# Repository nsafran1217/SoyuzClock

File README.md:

# SoyuzClock
Recreation of the 744H clock that flew on Soyuz space capsules

This is meant to be an accurate replica of the Soyuz 744H clock as feature on CuriousMarc's youtube channel.

- `SoyuzControlBoard` contains the KiCAD files for the esp32 board. There are many components that are optional.

- `SoyuzLedBoard` contains the KiCAD files for the board that the LED display mount on.

- `Soyuz-esp32` contains the PlatformIO project that runs the clock

## Part numbers
- АЛС324А is the 7 segment LED display. They are available on eBay or at tubes-store.com. They have the same quality issues as found in the real clock.

- МТ-1 is the toggle switch. They are available on eBay.

- ПКн2-1 is the correct push button, however, they are hard to find in the west. I found some stores selling them in Ukraine and Russia, but each switch is at least $15 US, plus you need to convince the seller its worth their time to ship it to you.

- KM1-1 is the next best option. They are easily found on eBay. The push button is smaller than the real switch. This is what I am using for now.

# 
Thanks to Curious Marc for documenting this clock: https://www.curiousmarc.com/space/soyuz-clock-744h-digital

I made a recreation of the case in FreeCAD based HEAVILY on this FreeCAD design: https://grabcad.com/library/soyuz-spacecraft-clock-1

This design will be added to this repo when finalized.

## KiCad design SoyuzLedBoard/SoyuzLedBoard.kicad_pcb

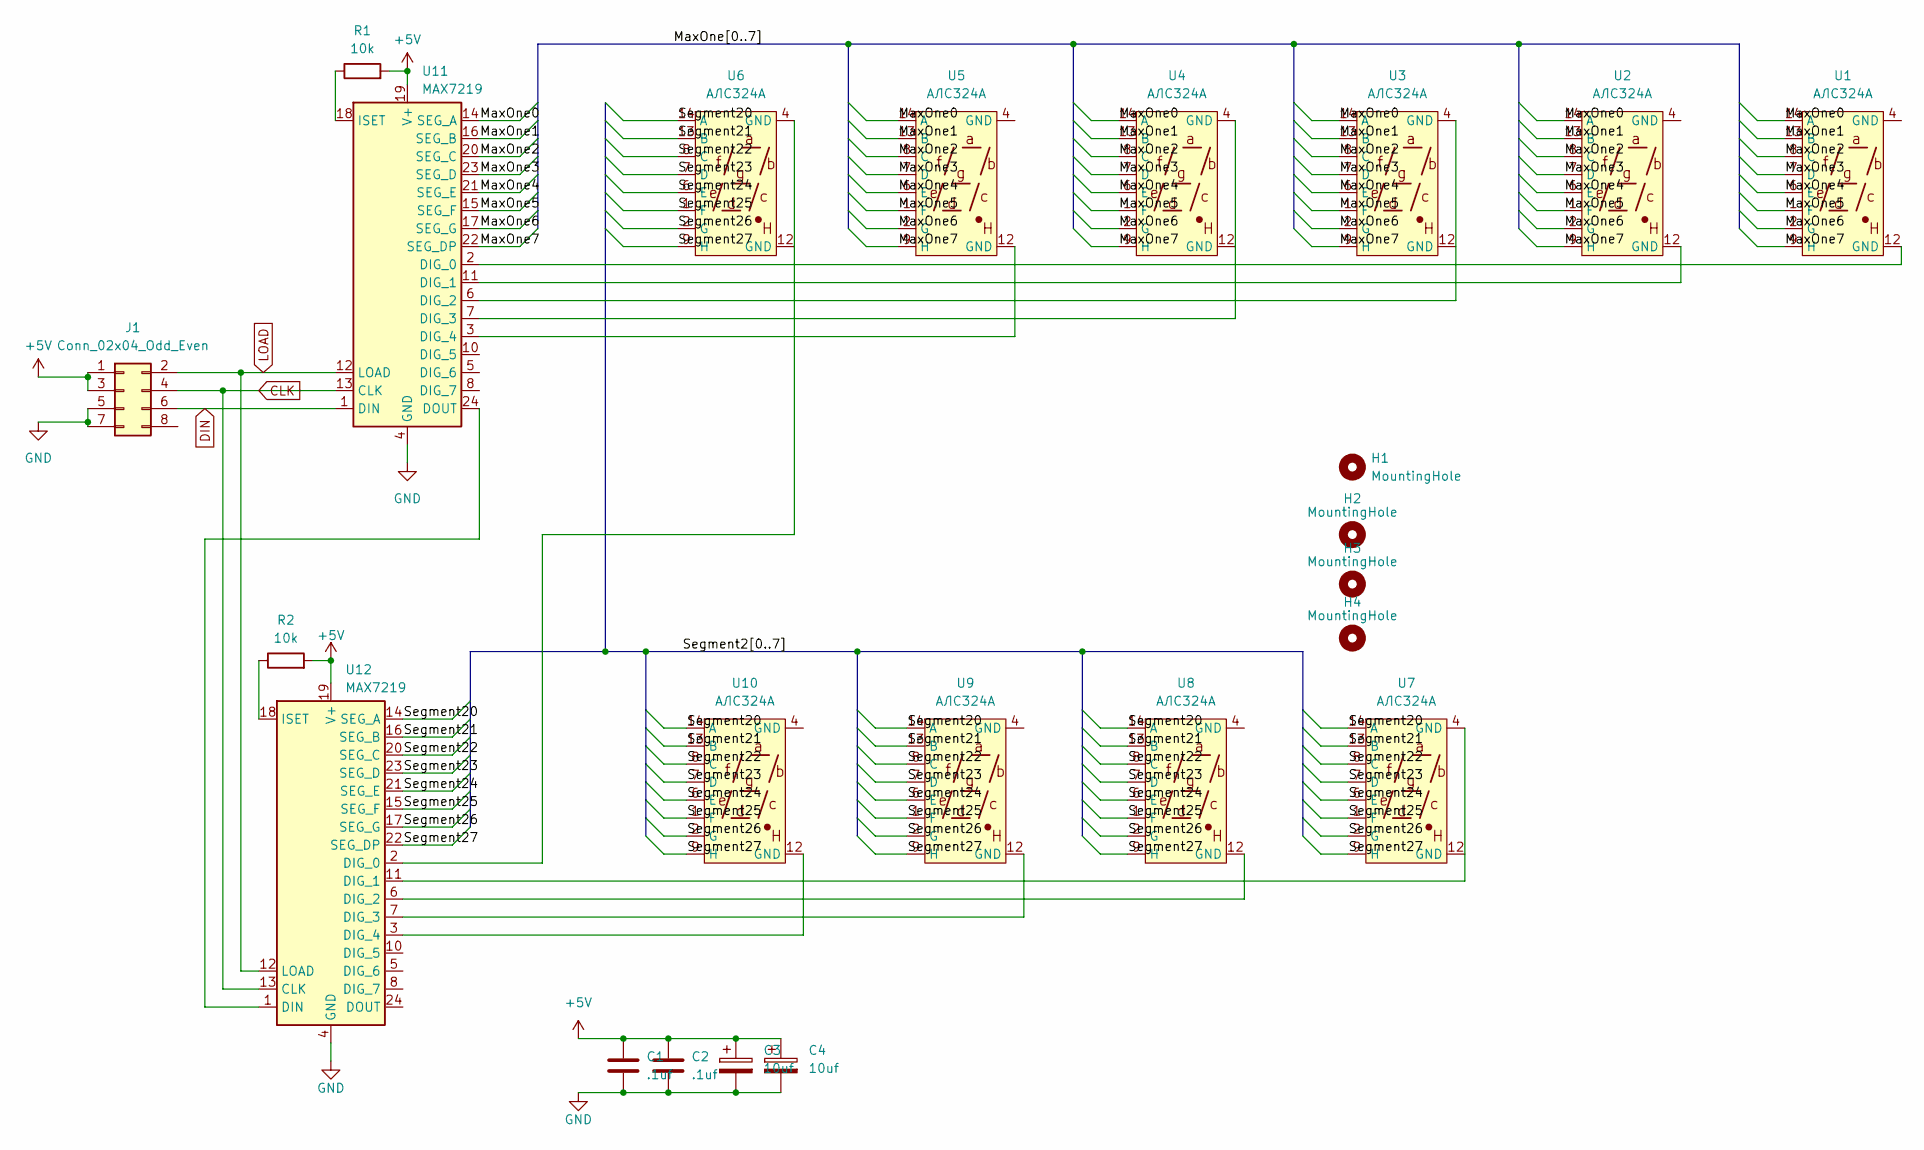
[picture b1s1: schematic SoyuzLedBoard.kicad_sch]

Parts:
C1, C2: .1uf; C_0805_2012Metric_Pad1.18x1.45mm_HandSolder
C3, C4: 10uf; CP_Radial_D4.0mm_P2.00mm
H1, H2, H3, H4: MountingHole; MountingHole_3.2mm_M3
J1: Conn_02x04_Odd_Even; PinHeader_2x04_P2.54mm_Vertical
R1, R2: 10k; R_0805_2012Metric_Pad1.20x1.40mm_HandSolder
U1, U2, U3, U4, U5, U6, U7, U8, U9, U10: АЛС324А; Metric-2.5mm DIP14
U11, U12: MAX7219; DIP-24_W7.62mm

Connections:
+5V: C1.1, C2.1, C3.1, C4.1, J1.1, J1.3, R1.2, R2.2, U11.19 (V+), U12.19 (V+)
/MaxOne0: U1.14 (A), U2.14 (A), U3.14 (A), U4.14 (A), U5.14 (A), U11.14 (SEG_A)
/MaxOne1: U1.13 (B), U2.13 (B), U3.13 (B), U4.13 (B), U5.13 (B), U11.16 (SEG_B)
/MaxOne2: U1.8 (C), U2.8 (C), U3.8 (C), U4.8 (C), U5.8 (C), U11.20 (SEG_C)
/MaxOne3: U1.7 (D), U2.7 (D), U3.7 (D), U4.7 (D), U5.7 (D), U11.23 (SEG_D)
/MaxOne4: U1.6 (E), U2.6 (E), U3.6 (E), U4.6 (E), U5.6 (E), U11.21 (SEG_E)
/MaxOne5: U1.1 (F), U2.1 (F), U3.1 (F), U4.1 (F), U5.1 (F), U11.15 (SEG_F)
/MaxOne6: U1.2 (G), U2.2 (G), U3.2 (G), U4.2 (G), U5.2 (G), U11.17 (SEG_G)
/MaxOne7: U1.9 (H), U2.9 (H), U3.9 (H), U4.9 (H), U5.9 (H), U11.22 (SEG_DP)
/Segment20: U6.14 (A), U7.14 (A), U8.14 (A), U9.14 (A), U10.14 (A), U12.14 (SEG_A)
/Segment21: U6.13 (B), U7.13 (B), U8.13 (B), U9.13 (B), U10.13 (B), U12.16 (SEG_B)
/Segment22: U6.8 (C), U7.8 (C), U8.8 (C), U9.8 (C), U10.8 (C), U12.20 (SEG_C)
/Segment23: U6.7 (D), U7.7 (D), U8.7 (D), U9.7 (D), U10.7 (D), U12.23 (SEG_D)
/Segment24: U6.6 (E), U7.6 (E), U8.6 (E), U9.6 (E), U10.6 (E), U12.21 (SEG_E)
/Segment25: U6.1 (F), U7.1 (F), U8.1 (F), U9.1 (F), U10.1 (F), U12.15 (SEG_F)
/Segment26: U6.2 (G), U7.2 (G), U8.2 (G), U9.2 (G), U10.2 (G), U12.17 (SEG_G)
/Segment27: U6.9 (H), U7.9 (H), U8.9 (H), U9.9 (H), U10.9 (H), U12.22 (SEG_DP)
CLK: J1.4, U11.13 (CLK), U12.13 (CLK)
DIN: J1.6, U11.1 (DIN)
GND: C1.2, C2.2, C3.2, C4.2, J1.5, J1.7, U11.4 (GND), U11.9 (GND), U12.4 (GND), U12.9 (GND)
LOAD: J1.2, U11.12 (LOAD), U12.12 (LOAD)
unnamed: U1.12 (GND), U11.2 (DIG_0)
unnamed: U2.12 (GND), U11.11 (DIG_1)
unnamed: U3.4 (GND), U11.6 (DIG_2)
unnamed: U4.4 (GND), U11.7 (DIG_3)
unnamed: U5.12 (GND), U11.3 (DIG_4)
unnamed: U11.24 (DOUT), U12.1 (DIN)
unnamed: R1.1, U11.18 (ISET)
unnamed: U6.4 (GND), U12.2 (DIG_0)
unnamed: U7.4 (GND), U12.11 (DIG_1)
unnamed: U8.12 (GND), U12.6 (DIG_2)
unnamed: U9.12 (GND), U12.7 (DIG_3)
unnamed: U10.12 (GND), U12.3 (DIG_4)
unnamed: R2.1, U12.18 (ISET)

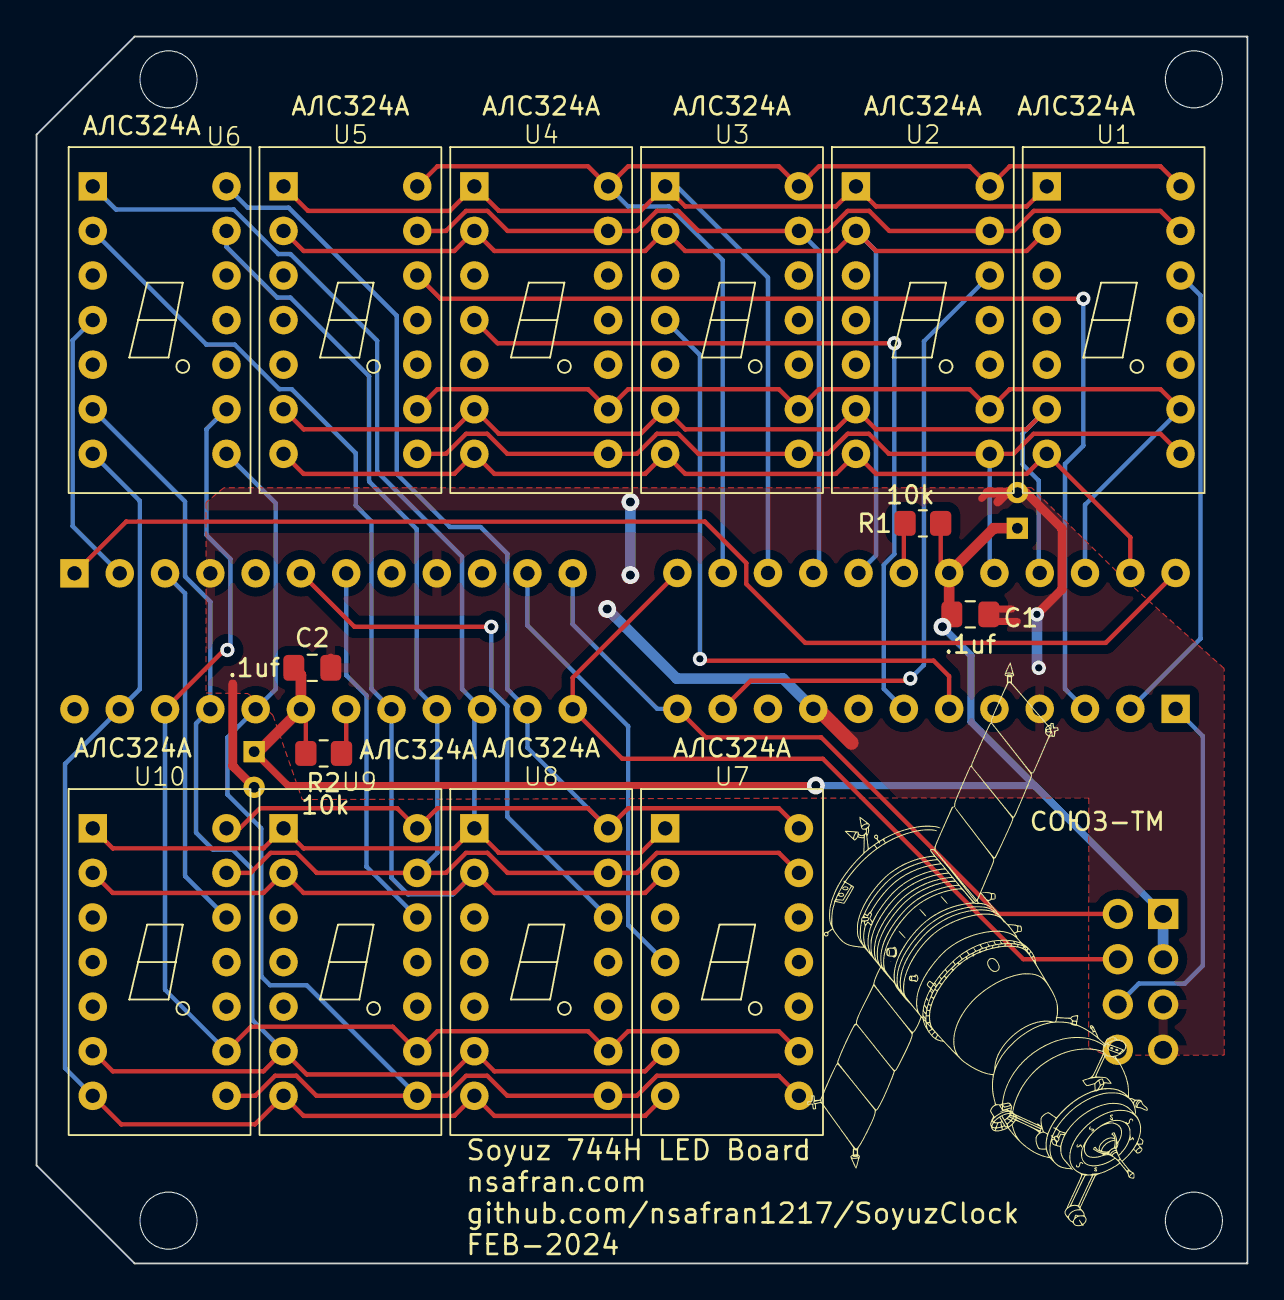
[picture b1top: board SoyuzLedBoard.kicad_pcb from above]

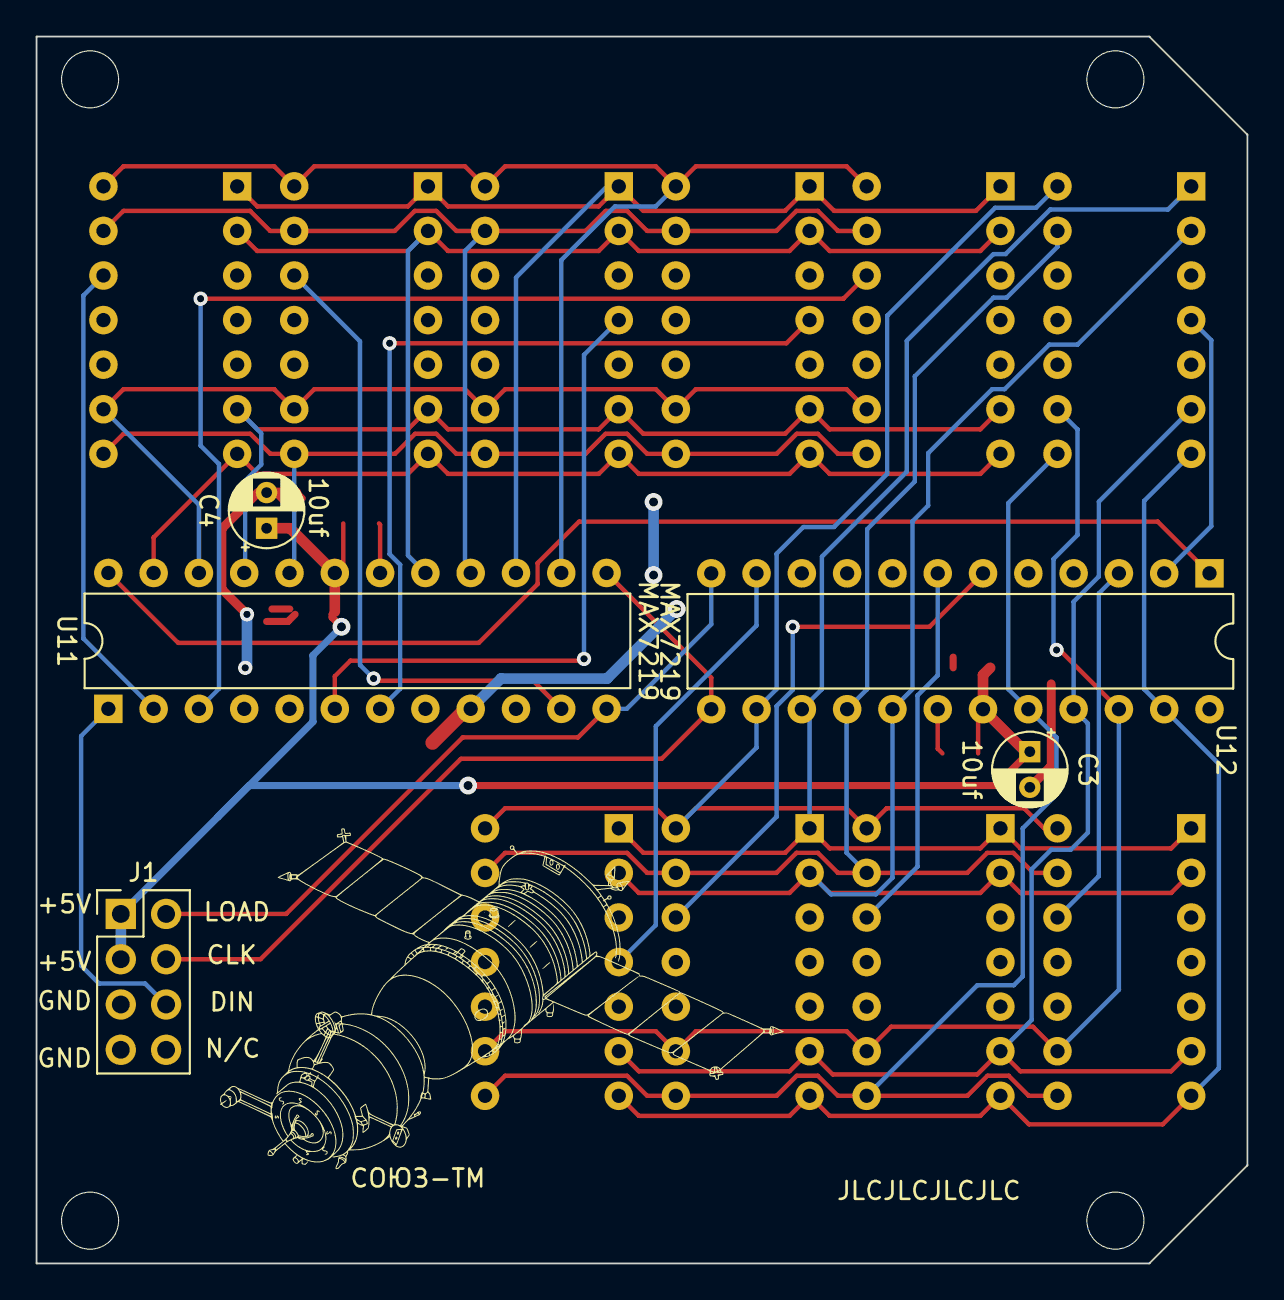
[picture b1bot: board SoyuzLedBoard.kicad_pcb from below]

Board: 2 copper layers, 67.9 x 68.8 mm, 23 parts (5 on the bottom side), 34 nets.

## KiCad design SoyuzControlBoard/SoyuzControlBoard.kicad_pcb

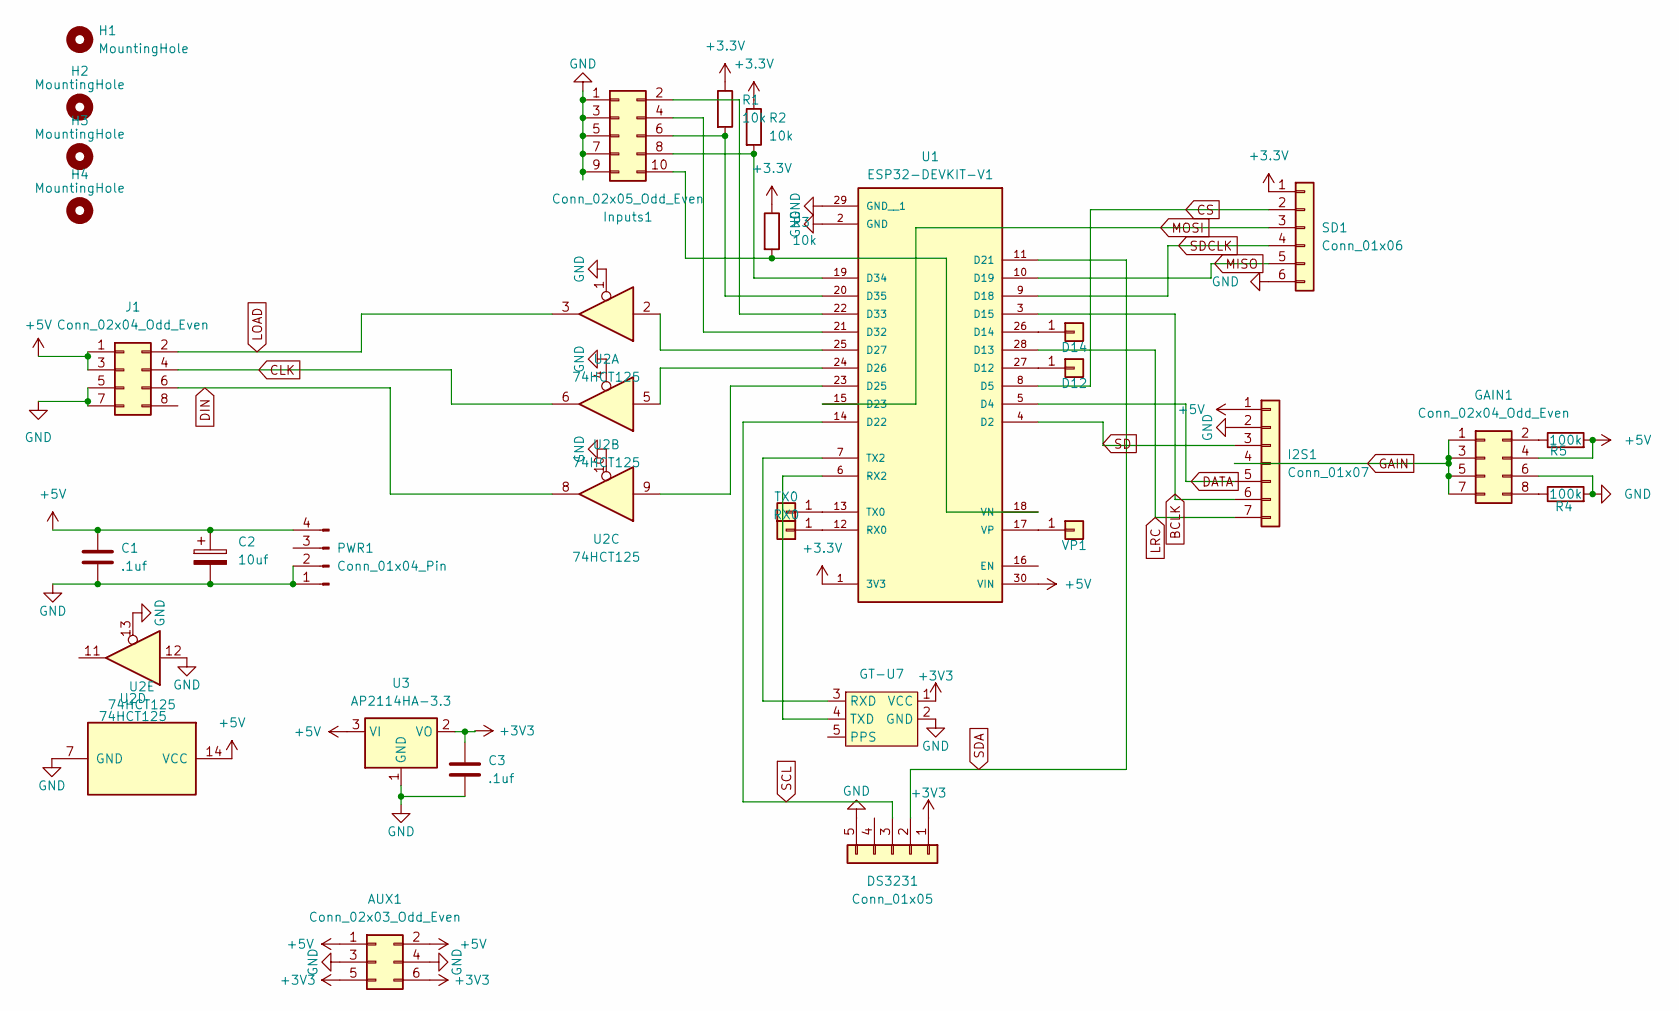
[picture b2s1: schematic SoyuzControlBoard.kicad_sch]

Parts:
AUX1: Conn_02x03_Odd_Even; PinHeader_2x03_P2.54mm_Vertical
C1, C3: .1uf; C_0805_2012Metric_Pad1.18x1.45mm_HandSolder
C2: 10uf; CP_Radial_D4.0mm_P2.00mm
D12, D14: Conn_01x01; 1x01
DS3231: Conn_01x05; PinHeader_1x05_P2.54mm_Vertical
GAIN1: Conn_02x04_Odd_Even; PinHeader_2x04_P2.54mm_Vertical
GT-U7: GT-U7_GPS
H1, H2, H3, H4: MountingHole; MountingHole_3.2mm_M3
I2S1: Conn_01x07; PinHeader_1x07_P2.54mm_Vertical
Inputs1: Conn_02x05_Odd_Even; IDC-Header_2x05_P2.54mm_Vertical
J1: Conn_02x04_Odd_Even; PinSocket_2x04_P2.54mm_Vertical
PWR1: Conn_01x04_Pin; PinHeader_1x04_P2.54mm_Vertical
R1, R2, R3: 10k; R_0805_2012Metric_Pad1.20x1.40mm_HandSolder
R4, R5: 100k; R_0805_2012Metric_Pad1.20x1.40mm_HandSolder
RX0: Conn_01x01; 1x01
SD1: Conn_01x06; PinHeader_1x06_P2.54mm_Vertical
TX0: Conn_01x01; 1x01
U1: ESP32-DEVKIT-V1; MODULE_ESP32_DEVKIT_V1; PARTREV N/A
U2: 74HCT125; DIP-14_W7.62mm
U3: AP2114HA-3.3; SOT-223-3_TabPin2
VP1: Conn_01x01; 1x01

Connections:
+3.3V: R1.1, R2.1, R3.1, SD1.1, U1.1 (3V3)
+3V3: AUX1.5, AUX1.6, C3.1, DS3231.1, GT-U7.1 (VCC), U3.2 (VO); also elsewhere on the board
+5V: AUX1.1, AUX1.2, C1.1, C2.1, GAIN1.4, I2S1.1, J1.1, J1.3, PWR1.4, R5.2, U1.30 (VIN), U2.14 (VCC), U3.3 (VI); also elsewhere on the board
BCLK: I2S1.6, U1.3 (D15)
CLK: J1.4, U2.6
CS: SD1.2, U1.8 (D5)
DATA: I2S1.5, U1.5 (D4)
DIN: J1.6, U2.8
GAIN: GAIN1.1, GAIN1.3, GAIN1.5, GAIN1.7, I2S1.4
GND: AUX1.3, AUX1.4, C1.2, C2.2, C3.2, DS3231.5, GAIN1.6, GT-U7.2 (GND), I2S1.2, Inputs1.1, Inputs1.3, Inputs1.5, Inputs1.7, Inputs1.9, J1.5, J1.7, PWR1.1, PWR1.2, R4.2, SD1.6, U1.2 (GND), U1.29 (GND__1), U2.1, U2.4, U2.7 (GND), U2.10, U2.12, U2.13, U3.1 (GND); also elsewhere on the board
LOAD: J1.2, U2.3
LRC: I2S1.7, U1.28 (D13)
MISO: SD1.5, U1.10 (D19)
MOSI: SD1.3, U1.15 (D23)
unnamed: D12.1, U1.27 (D12)
unnamed: D14.1, U1.26 (D14)
unnamed: GAIN1.2, R5.1
unnamed: GAIN1.8, R4.1
unnamed: GT-U7.3 (RXD), U1.7 (TX2)
unnamed: GT-U7.4 (TXD), U1.6 (RX2)
unnamed: Inputs1.2, U1.22 (D33)
unnamed: Inputs1.4, U1.21 (D32)
unnamed: Inputs1.6, R1.2, U1.20 (D35)
unnamed: Inputs1.8, R2.2, U1.19 (D34)
unnamed: Inputs1.10, R3.2, U1.18 (VN)
unnamed: RX0.1, U1.12 (RX0)
unnamed: TX0.1, U1.13 (TX0)
unnamed: U1.23 (D25), U2.9
unnamed: U1.24 (D26), U2.5
unnamed: U1.25 (D27), U2.2
unnamed: U1.17 (VP), VP1.1
SCL: DS3231.3, U1.14 (D22)
SD: I2S1.3, U1.4 (D2)
SDA: DS3231.2, U1.11 (D21)
SDCLK: SD1.4, U1.9 (D18)

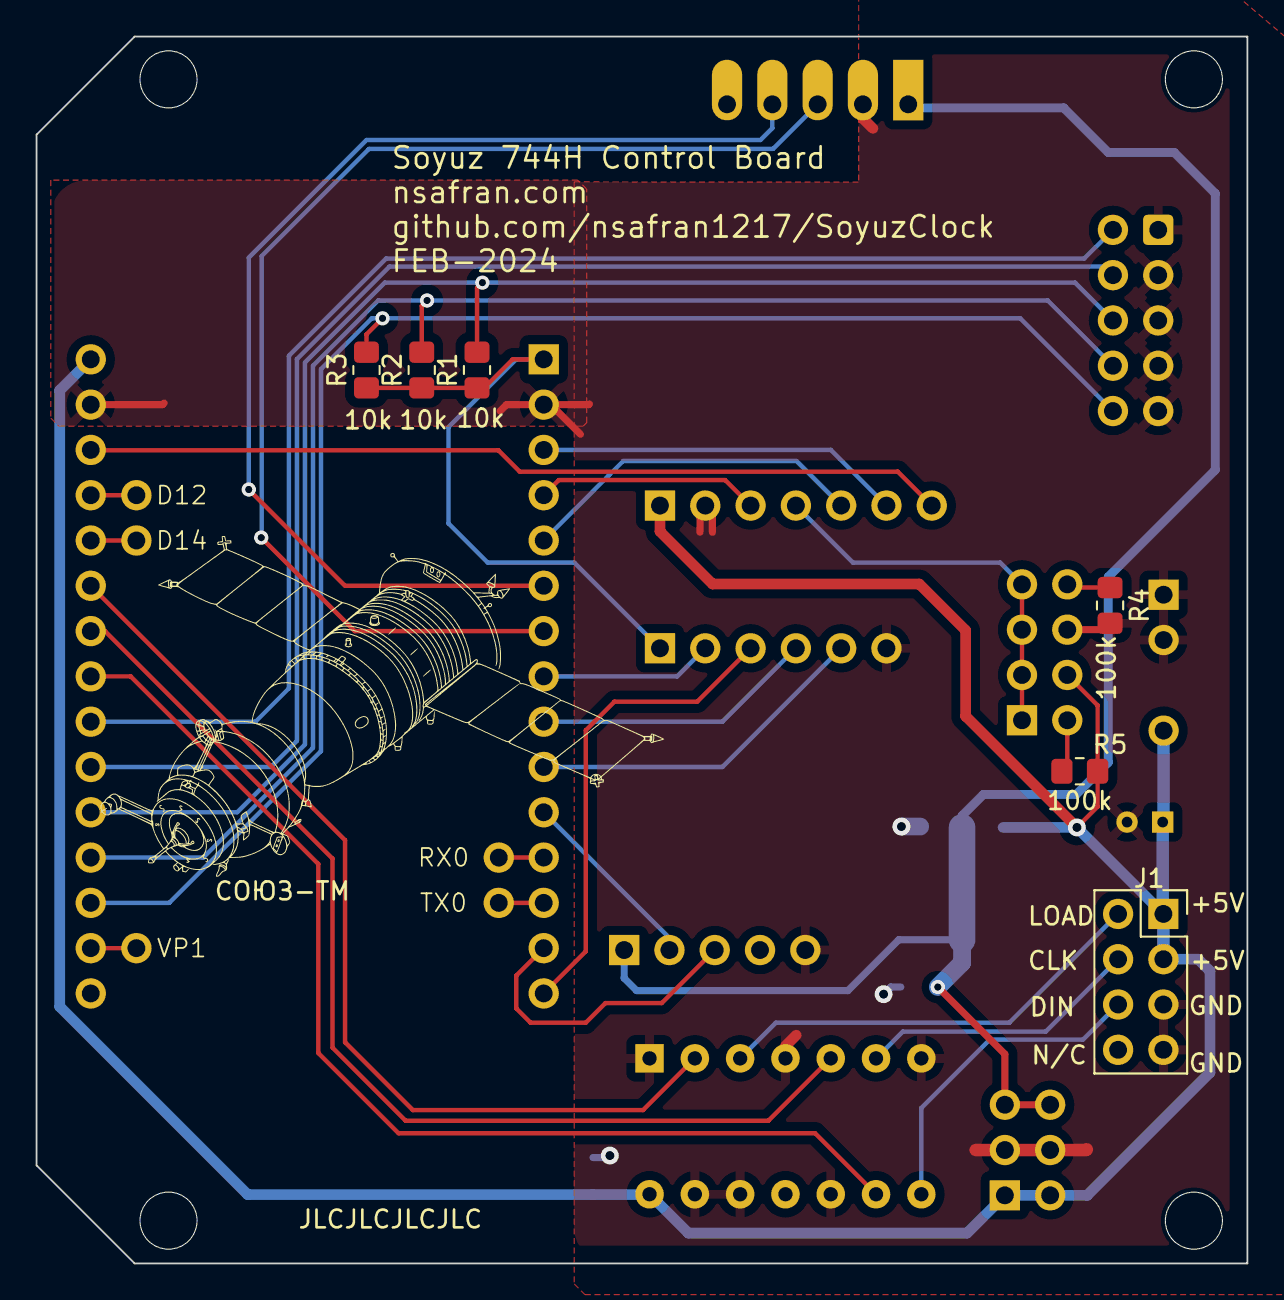
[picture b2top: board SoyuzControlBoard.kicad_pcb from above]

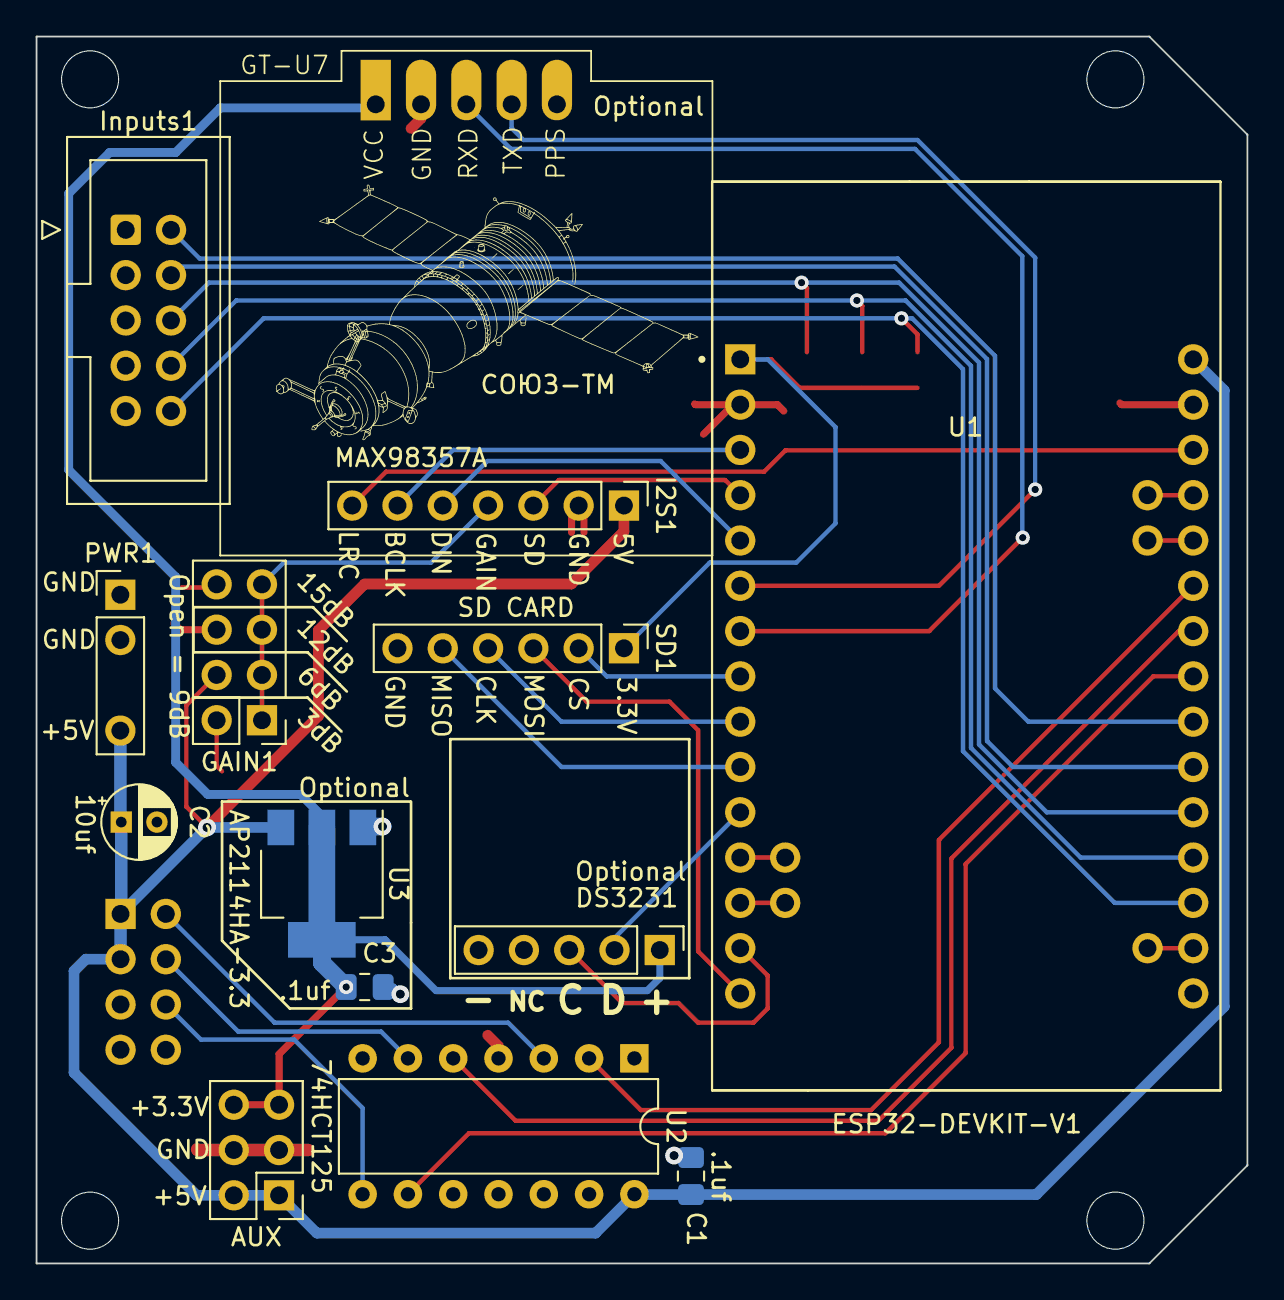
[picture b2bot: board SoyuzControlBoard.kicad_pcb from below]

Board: 2 copper layers, 67.9 x 68.8 mm, 29 parts (14 on the bottom side), 35 nets.

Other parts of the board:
AUX: Conn_02x03_Odd_Even; PinHeader_2x03_P2.54mm_Vertical

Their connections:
+3V3: AUX.5, AUX.6; also elsewhere on the board
+5V: AUX.1, AUX.2; also elsewhere on the board
GND: AUX.3, AUX.4; also elsewhere on the board

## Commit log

2024-02-17 Add KiCad designs
2024-02-17 init commit of code
2024-02-20 update gitignore
2024-02-20 Add write char functions
2024-02-20 add wifi functionality for setting params
2024-02-20 combine modes into main loop()
2024-04-16 Update README.md
    fix typos
